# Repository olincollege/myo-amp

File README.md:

To set it up for the first time, on Windows, run:

```ps1
./activate_scripts/new.ps1
```

On Linux/WSL/MacOS, run:
```bash
./activate_scripts/new.sh
```

If you already have a set up virtual environment but you want to activate it, just run:
```ps1
./activate_scripts/activate.ps1
```
on Windows, and in Linux/WSL, MacOS, run:
```bash
./activate_scripts/activate.sh
```

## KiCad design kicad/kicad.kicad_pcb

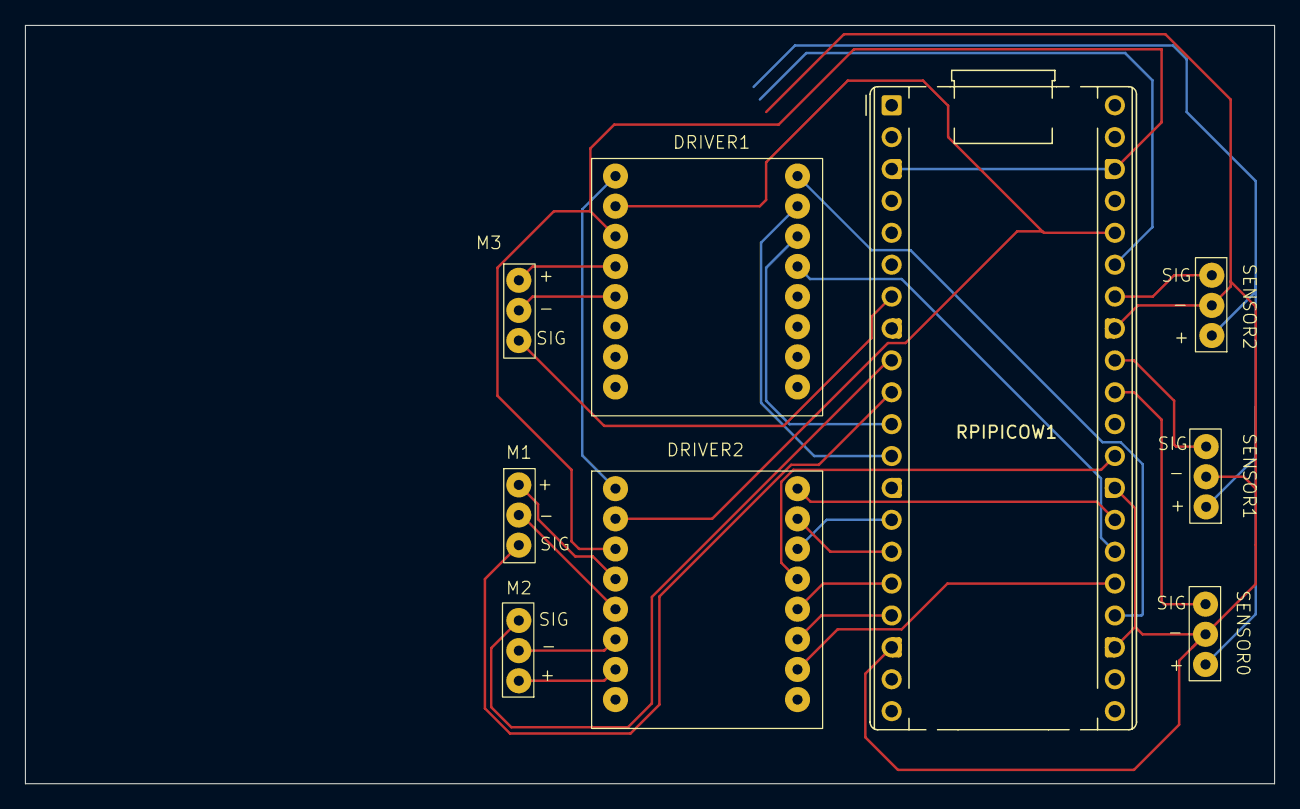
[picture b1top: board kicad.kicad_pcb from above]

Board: 2 copper layers, 99.5 x 60.4 mm, 9 parts (0 on the bottom side), 27 nets.

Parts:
DRIVER1, DRIVER2: TB6612FNG; Motor_Driver_Breakout
M1, M2, M3: DC Motor (w/ Encoders); Untitled_1
RPIPICOW1: Raspberry Pi Pico W; RaspberryPi_Pico_Common_THT
SENSOR0, SENSOR1, SENSOR2: SEN-13723; Untitled_1

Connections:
+3V0: RPIPICOW1.35 (ADC_VREF), SENSOR0.1 (VS), SENSOR1.1 (VS), SENSOR2.1 (VS)
+3V3: DRIVER1.15 (Vcc), DRIVER2.15 (Vcc), RPIPICOW1.36 (3V3)
+12V: DRIVER1.16 (VM1), DRIVER2.16 (VM1)
GNDREF: DRIVER1.14 (GND), DRIVER2.14 (GND), RPIPICOW1.3 (GND), RPIPICOW1.8 (GND), RPIPICOW1.13 (GND), RPIPICOW1.18 (GND), RPIPICOW1.23 (GND), RPIPICOW1.28 (GND), RPIPICOW1.33 (AGND), RPIPICOW1.38 (GND), SENSOR0.2 (GND), SENSOR1.2 (GND), SENSOR2.2 (GND)
unnamed: DRIVER1.3 (AIN1), RPIPICOW1.11 (GPIO8)
unnamed: DRIVER1.2 (AIN2), RPIPICOW1.12 (GPIO9)
unnamed: DRIVER1.1 (PWMA), RPIPICOW1.24 (GPIO18)
unnamed: DRIVER1.4 (STBY), RPIPICOW1.26 (GPIO20)
unnamed: DRIVER2.3 (AIN1), RPIPICOW1.14 (GPIO10)
unnamed: DRIVER2.2 (AIN2), RPIPICOW1.15 (GPIO11)
unnamed: DRIVER2.5 (BIN1), RPIPICOW1.16 (GPIO12)
unnamed: DRIVER2.6 (BIN2), RPIPICOW1.17 (GPIO13)
unnamed: DRIVER2.1 (PWMA), RPIPICOW1.27 (GPIO21)
unnamed: DRIVER2.7 (PWMB), RPIPICOW1.25 (GPIO19)
unnamed: DRIVER2.4 (STBY), RPIPICOW1.29 (GPIO22)
unnamed: DRIVER2.13 (AO1), M1.1 (+)
unnamed: DRIVER2.12 (AO2), M1.2 (-)
unnamed: M1.3 (EN), RPIPICOW1.10 (GPIO7)
unnamed: DRIVER2.10 (BO1), M2.1 (+)
unnamed: DRIVER2.8 (BO2), DRIVER2.11 (BO2), M2.2 (-)
unnamed: M2.3 (EN), RPIPICOW1.9 (GPIO6)
unnamed: DRIVER1.13 (AO1), M3.1 (+)
unnamed: DRIVER1.6 (AO2), DRIVER1.12 (AO2), M3.2 (-)
unnamed: M3.3 (EN), RPIPICOW1.7 (GPIO5)
unnamed: RPIPICOW1.31 (GPIO26_ADC0), SENSOR0.3 (SIG)
unnamed: RPIPICOW1.32 (GPIO27_ADC1), SENSOR1.3 (SIG)
unnamed: RPIPICOW1.34 (GPIO28_ADC2), SENSOR2.3 (SIG)

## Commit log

2025-10-24 microcontroller init
2025-10-28 second initial commit; added activation scripts for easy virtual environments
2025-11-05 added pi pico and arduino data collection files; both untested
2025-11-05 added python script to read data from arduino and convert it to csv
2025-11-10 updated logic to work for 1 pico
2025-11-10 added kicad logic files
2025-11-10 added pico datasheet and resources folder
2025-11-13 training data
2025-11-13 added motor driver and motors to schematic; left space for future motors with encoders
2025-11-13 edited code to match kicad
2025-11-13 kicad schematic mostly finished; struggling with footprints; updated pico code to match schematic
2025-11-16 pcb mostly finished
2025-11-16 pcb edits and flip
2025-11-16 upload updated kiCAD files
2025-11-17 cleaned data
2025-11-17 ml working w confusion matrix
2025-12-13 compiling, remade version of microcontroller code in the C++ sdk; untested
2025-12-16 debugged state to fix tons of issues about memory
2025-12-16 added documentation
2025-12-16 motor driver pdf resources
2025-12-17 added subclass to get DRV8871 working
2025-12-17 added simple documentation to DRV8871 motor driver pins
2025-12-17 functioning ml library
2025-12-17 plsss work
2025-12-17 ml start setup
